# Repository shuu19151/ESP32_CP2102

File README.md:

# ESP32_CP2102

## PCB design for external programmer board for ESP32 using CP2102 USB to TTL IC.  
### _Front view_:

### _Back view_:

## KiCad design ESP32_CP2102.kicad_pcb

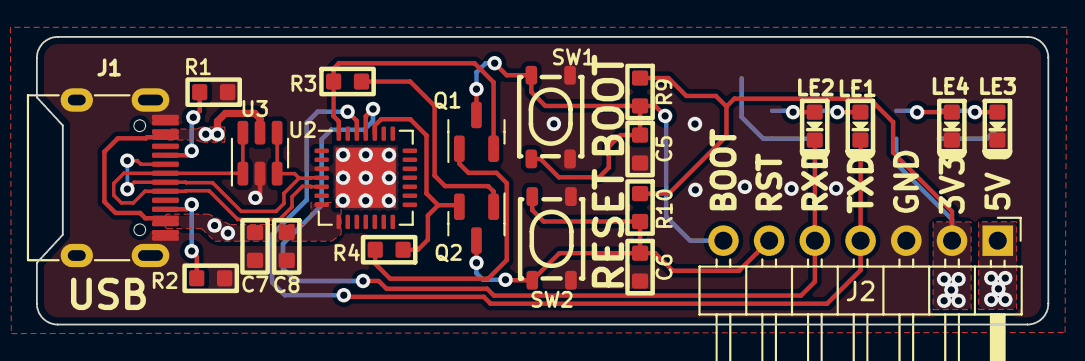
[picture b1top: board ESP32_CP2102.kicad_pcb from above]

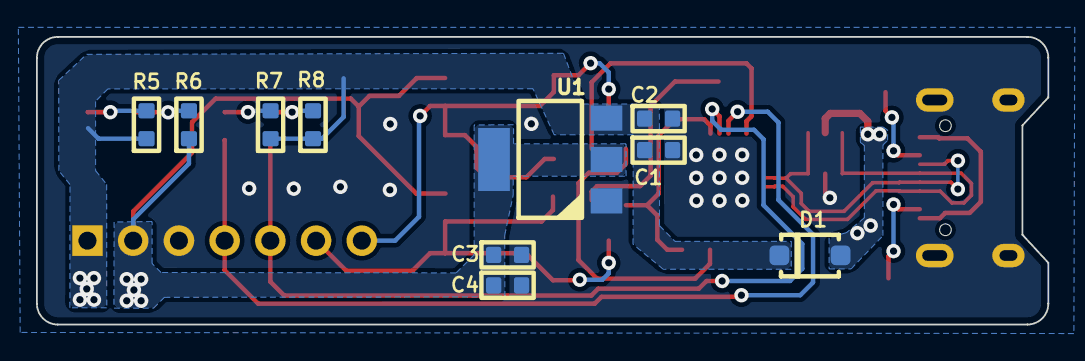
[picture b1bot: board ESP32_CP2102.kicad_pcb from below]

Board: 2 copper layers, 56.2 x 16.0 mm, 32 parts (10 on the bottom side), 20 nets.

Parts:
C1, C4, C5, C7: 100nF; C_0603
C2, C3, C6, C8: 10uF; C_0603
D1: D_Schottky; Package-Diode-D_SOD_123
J1: USB_C_Receptacle; USB_C_Receptacle_XKB_U262-16XN-4BVC11
J2: Conn_01x07; PinHeader_1x07_P2.54mm_Horizontal
LE1, LE2, LE3, LE4: Led; LED_0603
Q1, Q2: MMBT3904; SOT-23
R1, R2: 5k1; R_0603
R3, R4, R7, R8, R9, R10: 10k; R_0603
R5, R6: 1k; R_0603
SW1, SW2: SW_Push; ButtonPush-Vert-SMD-4P-SPST_PTS810
U1: AMS1117; SOT233
U2: CP2102N-Axx-xQFN28; QFN-28-1EP_5x5mm_P0.5mm_EP3.35x3.35mm
U3: SRV05-4; SOT-23-6

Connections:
+3V3: C3.1, C4.1, J2.2, R6.1, R9.1, R10.1, U1.2 (VO)
+5V: C1.1, C2.1, D1.2, J2.1, R5.1, R7.1, R8.1, U1.3 (VI)
BOOT: C5.1, J2.7, Q1.3 (C), R9.2, SW1.1
D+: J1.A6 (D+), J1.B6 (D+), U2.5 (D-), U3.1 (IO1), U3.6 (IO4)
D-: J1.A7 (D-), J1.B7 (D-), U2.4 (D+), U3.3 (IO2), U3.4 (IO3)
DTR: Q1.2 (E), R3.1, U2.28 (~DTR)
GND: C1.2, C2.2, C3.2, C4.2, C5.2, C6.2, C7.2, C8.2, J1.A1 (GND), J1.A12 (GND), J1.B1 (GND), J1.B12 (GND), J1.S1 (SHIELD), J2.3, LE3.2, LE4.2, R1.1, R2.1, SW1.2, SW2.1, U1.1 (GND), U2.3 (GND), U2.29 (GND), U3.2 (VN)
unnamed: J1.A5 (CC1), R1.2
unnamed: J1.B5 (CC2), R2.2
unnamed: LE1.1, R7.2
unnamed: LE2.1, R8.2
unnamed: LE3.1, R5.2
unnamed: LE4.1, R6.2
unnamed: Q1.1 (B), R4.2
unnamed: Q2.1 (B), R3.2
RST: C6.1, J2.6, Q2.3 (C), R10.2, SW2.2
RTS: Q2.2 (E), R4.1, U2.24 (~RTS)
RXD: J2.5, LE2.2, U2.25 (RXD)
TXD: J2.4, LE1.2, U2.26 (TXD)
VBUS: C7.1, C8.1, D1.1, J1.A4 (VBUS), J1.A9 (VBUS), J1.B4 (VBUS), J1.B9 (VBUS), U2.7 (VREGIN), U2.8 (VBUS), U3.5 (VP)

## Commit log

2023-08-24 Add README.md
